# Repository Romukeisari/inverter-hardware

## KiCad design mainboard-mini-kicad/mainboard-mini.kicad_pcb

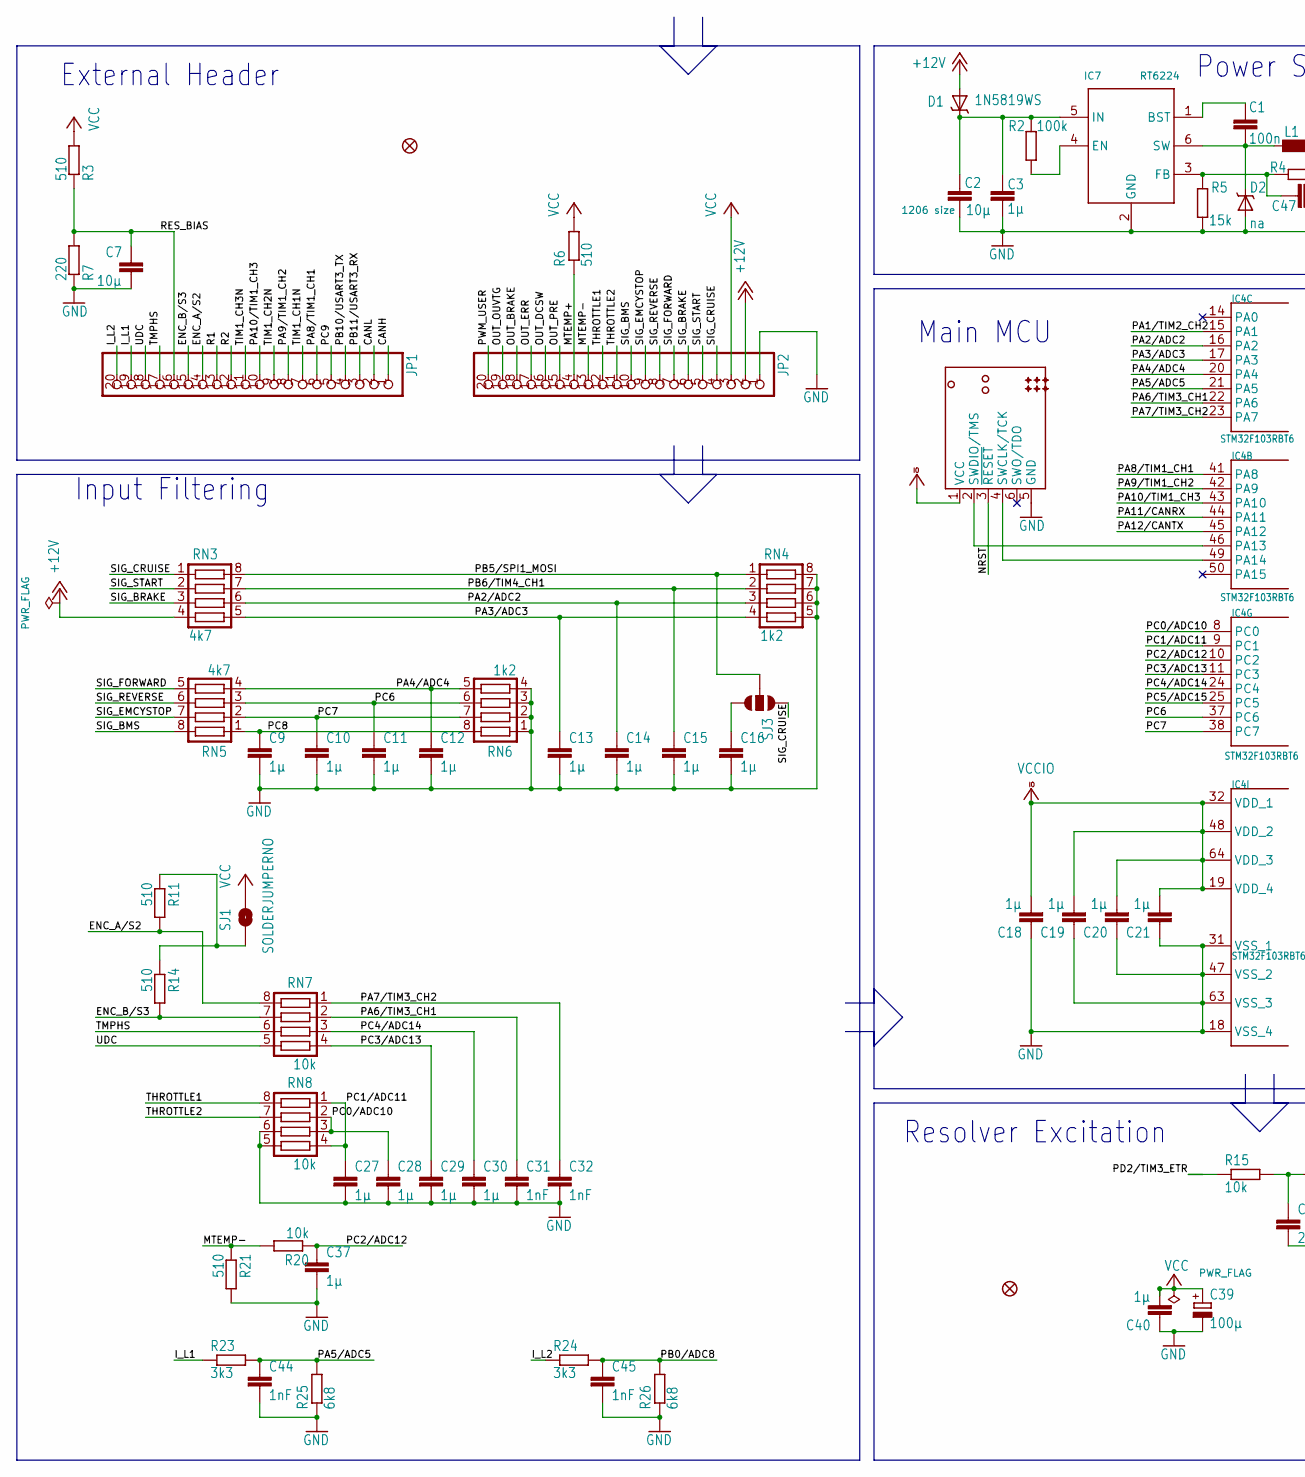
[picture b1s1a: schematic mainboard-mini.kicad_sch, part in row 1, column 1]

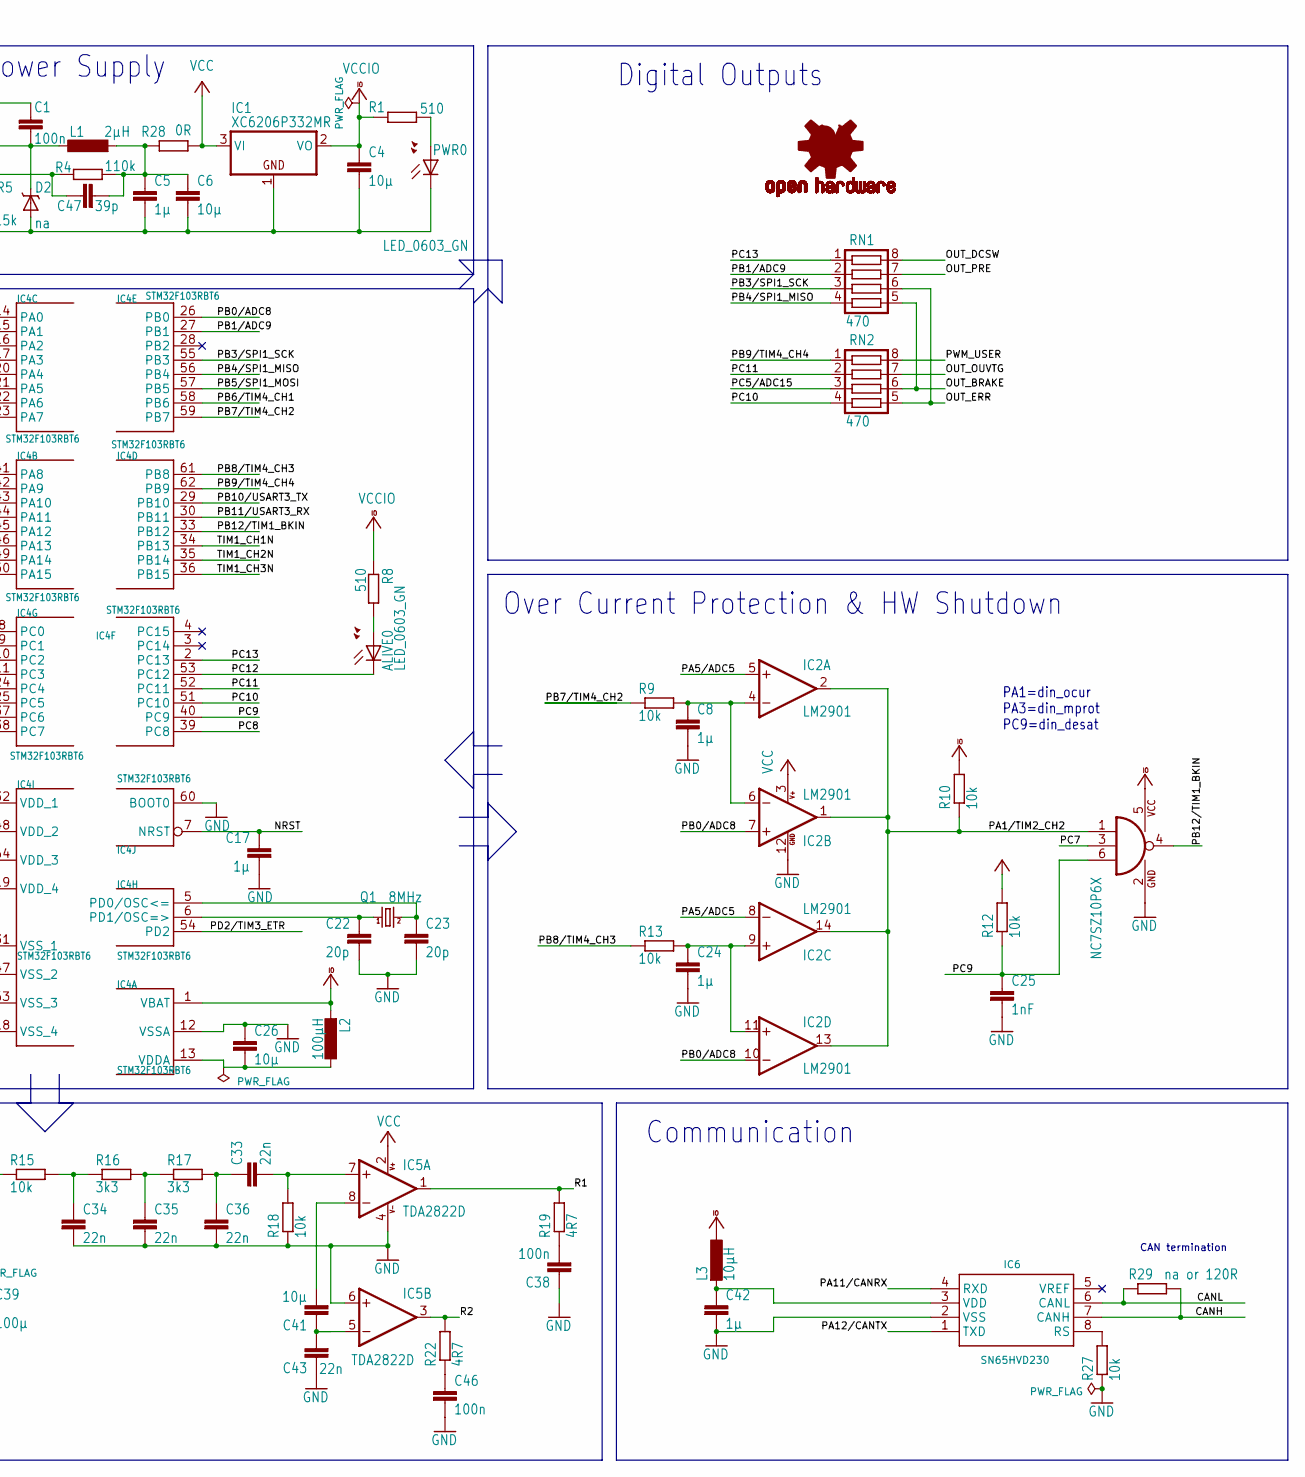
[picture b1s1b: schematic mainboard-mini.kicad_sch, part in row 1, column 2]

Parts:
ALIVE0: LED_0603_GN; SML0805
C1, C38, C46: 100n; C0603
C2: 10µ; C_1206_3216Metric
C3, C5, C8, C9, C10, C11, C12, C13, C14, C15, C16, C17, C18, C19, C20, C21, C24, C27, C28, C29, C30, C37, C40, C42: 1µ; C0603
C4, C6, C7, C26, C41: 10µ; C0603
C22, C23: 20p; C0603
C25, C31, C32, C44, C45: 1nF; C0603
C33, C34, C35, C36, C43: 22n; C0603
C39: 100µ; B_3528-21R
C47: 39p; C_0603_1608Metric
D1: 1N5819WS; SOD-323
D2: na; SOD-323
FID1, FID2: FIDUCIAL1X2.5; FIDUCIAL-1X2.5
IC1: XC6206P332MR; SOT23
IC2: LM2901; SO14
IC3: NC7SZ10P6X; SC70-6
IC4: STM32F103RBT6; TQFP64
IC5: TDA2822D; SO08
IC6: SN65HVD230; SO08
IC7: RT6224; SOT23-6
J1: TC2030_SWD-MCP; TC2030-MCP
JP1, JP2: PINHD-1X20; 1X20
L1: 2µH; L2825P
L2: 100µH; L2012C
L3: 10µH; L2012C
LOGO1: OSHW-LOGOM; OSHW-LOGO-M
PWR0: LED_0603_GN; SML0805
Q1: 8MHz; CRYSTAL-TXC-7A
R1, R3, R6, R8, R11, R14, R21: 510; R0603
R2: 100k; R0603
R4: 110k; R0603
R5: 15k; R0603
R7: 220; R0603
R9, R10, R12, R13, R15, R18, R20, R27: 10k; R0603
R16, R17, R23, R24: 3k3; R0603
R19, R22: 4R7; R0603
R25, R26: 6k8; R0603
R28: 0R; R_0805_2012Metric
R29: na or 120R; R_0603_1608Metric
RN1, RN2: 470; CTS742C083
RN3, RN5: 4k7; CTS742C083
RN4, RN6: 1k2; CTS742C083
RN7, RN8: 10k; CTS742C083
SJ1: SOLDERJUMPERNO; SJ_2S-NO
SJ3: SOLDERJUMPER_2WAYPASTE2&3; SJ_3_PASTE2&3

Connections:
+12V: D1.2 (A), JP2.2, RN3.4
/CANH: IC6.7 (CANH), JP1.1, R29.2
/CANL: IC6.6 (CANL), JP1.2, R29.1
/ENC_A/S2: JP1.14, R11.2, RN7.8
/ENC_B/S3: JP1.15, R14.2, RN7.7
/I_L1: JP1.19, R23.1
/I_L2: JP1.20, R24.1
/MTEMP+: JP2.14, R6.1
/MTEMP-: JP2.13, R20.2, R21.1
/NRST: C17.1, IC4.7 (NRST), J1.3 (~RESET)
/OUT_BRAKE: JP2.18, RN1.5, RN2.6
/OUT_DCSW: JP2.16, RN1.8
/OUT_ERR: JP2.17, RN1.6, RN2.5
/OUT_OUVTG: JP2.19, RN2.7
/OUT_PRE: JP2.15, RN1.7
/PA1/TIM2_CH2: IC2.1 (OUT), IC2.2 (OUT), IC2.13 (OUT), IC2.14 (OUT), IC3.1 (I0), IC4.15 (PA1), R10.1
/PA2/ADC2: C14.1, IC4.16 (PA2), RN3.6, RN4.3
/PA3/ADC3: C13.1, IC4.17 (PA3), RN3.5, RN4.4
/PA4/ADC4: C12.1, IC4.20 (PA4), RN5.4, RN6.5
/PA5/ADC5: C44.1, IC2.5 (+IN), IC2.8 (-IN), IC4.21 (PA5), R23.2, R25.2
/PA6/TIM3_CH1: C31.1, IC4.22 (PA6), RN7.2
/PA7/TIM3_CH2: C32.1, IC4.23 (PA7), RN7.1
/PA8/TIM1_CH1: IC4.41 (PA8), JP1.6
/PA9/TIM1_CH2: IC4.42 (PA9), JP1.8
/PA10/TIM1_CH3: IC4.43 (PA10), JP1.10
/PA11/CANRX: IC4.44 (PA11), IC6.4 (RXD)
/PA12/CANTX: IC4.45 (PA12), IC6.1 (TXD)
/PB0/ADC8: C45.1, IC2.7 (+IN), IC2.10 (-IN), IC4.26 (PB0), R24.2, R26.2
/PB1/ADC9: IC4.27 (PB1), RN1.2
/PB3/SPI1_SCK: IC4.55 (PB3), RN1.3
/PB4/SPI1_MISO: IC4.56 (PB4), RN1.4
/PB5/SPI1_MOSI: IC4.57 (PB5), RN3.8, RN4.1, SJ3.2
/PB6/TIM4_CH1: C15.1, IC4.58 (PB6), RN3.7, RN4.2
/PB7/TIM4_CH2: IC4.59 (PB7), R9.1
/PB8/TIM4_CH3: IC4.61 (PB8), R13.1
/PB9/TIM4_CH4: IC4.62 (PB9), RN2.1
/PB10/USART3_TX: IC4.29 (PB10), JP1.4
/PB11/USART3_RX: IC4.30 (PB11), JP1.3
/PB12/TIM1_BKIN: IC3.4 (O), IC4.33 (PB12)
/PC0/ADC10: C28.1, IC4.8 (PC0), RN8.2, RN8.3
/PC1/ADC11: C27.1, IC4.9 (PC1), RN8.1, RN8.4
/PC2/ADC12: C37.1, IC4.10 (PC2), R20.1
/PC3/ADC13: C29.1, IC4.11 (PC3), RN7.4
/PC4/ADC14: C30.1, IC4.24 (PC4), RN7.3
/PC5/ADC15: IC4.25 (PC5), RN2.3
/PC6: C11.1, IC4.37 (PC6), RN5.3, RN6.6
/PC7: C10.1, IC3.3 (I1), IC4.38 (PC7), RN5.2, RN6.7
/PC8: C9.1, IC4.39 (PC8), RN5.1, RN6.8
/PC9: C25.1, IC3.6 (I2), IC4.40 (PC9), JP1.5, R12.1
/PC10: IC4.51 (PC10), RN2.4
/PC11: IC4.52 (PC11), RN2.2
/PC12: ALIVE0.C, IC4.53 (PC12)
/PC13: IC4.2 (PC13), RN1.1
/PD2/TIM3_ETR: IC4.54 (PD2), R15.1
/PWM_USER: JP2.20, RN2.8
/R1: IC5.1 (OUT), JP1.13, R19.2
/R2: IC5.3 (OUT), JP1.12, R22.2
/RES_BIAS: C7.1, JP1.16, R3.1, R7.2
/SIG_BMS: JP2.10, RN5.8
/SIG_BRAKE: JP2.6, RN3.3
/SIG_CRUISE: JP2.4, RN3.1, SJ3.1
/SIG_EMCYSTOP: JP2.9, RN5.7
/SIG_FORWARD: JP2.7, RN5.5
/SIG_REVERSE: JP2.8, RN5.6
/SIG_START: JP2.5, RN3.2
/THROTTLE1: JP2.12, RN8.8
/THROTTLE2: JP2.11, RN8.7
/TIM1_CH1N: IC4.34 (PB13), JP1.7
/TIM1_CH2N: IC4.35 (PB14), JP1.9
/TIM1_CH3N: IC4.36 (PB15), JP1.11
/TMPHS: JP1.17, RN7.6
/UDC: JP1.18, RN7.5
GND: C2.2, C3.2, C4.2, C5.2, C6.2, C7.2, C8.2, C9.2, C10.2, C11.2, C12.2, C13.2, C14.2, C15.2, C16.2, C17.2, C18.1, C19.1, C20.1, C21.1, C22.2, C23.2, C24.2, C25.2, C26.1, C27.2, C28.2, C29.2, C30.2, C31.2, C32.2, C34.2, C35.2, C36.2, C37.2, C38.1, C39.-, C40.1, C42.2, C43.1, C44.2, C45.2, C46.2, D2.2 (A), IC1.1 (GND), IC2.12 (GND), IC3.2 (GND), IC4.12 (VSSA), IC4.18 (VSS_4), IC4.31 (VSS_1), IC4.47 (VSS_2), IC4.60 (BOOT0), IC4.63 (VSS_3), IC5.4 (V-), IC5.6 (+IN), IC6.2 (VSS), IC7.2 (GND), J1.5 (GND), JP2.1, PWR0.C, R5.1, R7.1, R18.1, R21.2, R25.1, R26.1, R27.1, RN4.5, RN4.6, RN4.7, RN4.8, RN6.1, RN6.2, RN6.3, RN6.4, RN8.5, RN8.6
unnamed: ALIVE0.A, R8.2
unnamed: C16.1, SJ3.3
unnamed: C33.1, C36.1, R17.2
unnamed: C34.1, R15.2, R16.1
unnamed: C35.1, R16.2, R17.1
unnamed: C38.2, R19.1
unnamed: C46.1, R22.1
unnamed: C5.1, C6.1, C47.2, L1.2, R4.1, R28.2
unnamed: C2.1, C3.1, D1.1 (C), IC7.5 (IN), R2.2
unnamed: C1.2, D2.1 (C), IC7.6 (SW), L1.1
unnamed: C8.1, IC2.4 (-IN), IC2.6 (-IN), R9.2
unnamed: C24.1, IC2.9 (+IN), IC2.11 (+IN), R13.2
unnamed: C26.2, IC4.13 (VDDA), L2.1
unnamed: IC4.46 (PA13), J1.2 (SWDIO/TMS)
unnamed: IC4.49 (PA14), J1.4 (SWCLK/TCK)
unnamed: C23.1, IC4.5 (PD0/OSC<=), Q1.P$2 (2)
unnamed: C22.1, IC4.6 (PD1/OSC=>), Q1.P$1 (1)
unnamed: C33.2, IC5.7 (+IN), R18.2
unnamed: C41.2, IC5.8 (-IN)
unnamed: C41.1, C43.2, IC5.5 (-IN)
unnamed: IC6.8 (RS), R27.2
unnamed: C42.1, IC6.3 (VDD), L3.2
unnamed: C1.1, IC7.1 (BST)
unnamed: IC7.4 (EN), R2.1
unnamed: C47.1, IC7.3 (FB), R4.2, R5.2
unnamed: PWR0.A, R1.2
unnamed: R11.1, R14.1, SJ1.1
VCC: C39.+, C40.2, IC1.3 (VI), IC2.3 (V+), IC5.2 (V+), JP2.3, R3.2, R6.2, R12.2, R28.1, SJ1.2
VCCIO: C4.1, C18.2, C19.2, C20.2, C21.2, IC1.2 (VO), IC3.5 (VCC), IC4.1 (VBAT), IC4.19 (VDD_4), IC4.32 (VDD_1), IC4.48 (VDD_2), IC4.64 (VDD_3), J1.1 (VCC), L2.2, L3.1, R1.1, R8.1, R10.2

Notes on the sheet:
Power Supply
CAN termination
Digital Outputs
PA1=din_ocur PA3=din_mprot PC9=din_desat
Main MCU
External Header
Over Current Protection & HW Shutdown
Communication
Input Filtering
Resolver Excitation

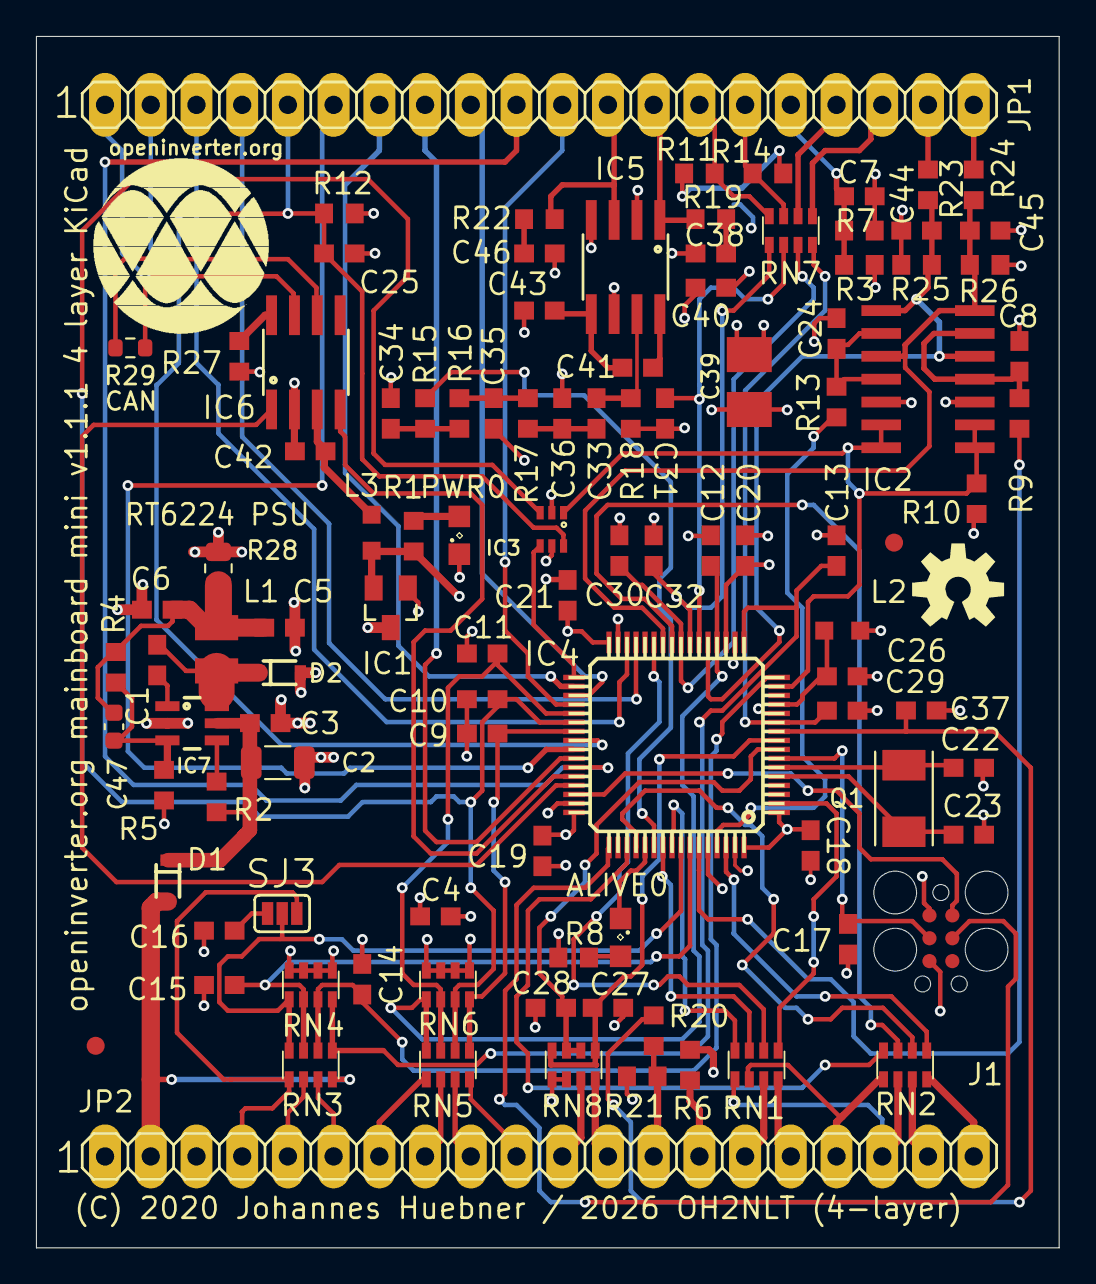
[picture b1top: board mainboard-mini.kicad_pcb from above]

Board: 4 copper layers, 56.8 x 67.3 mm, 108 parts (1 on the bottom side), 102 nets.

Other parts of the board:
U$2: OI_LOGO

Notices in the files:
mainboard-mini-kicad/mainboard-mini.kicad_pcb:
(C) 2020 Johannes Huebner / 2026 OH2NLT (4-layer)
parts and their libraries:
PADDescription 1MCLR/Vpp 2Vdd 3GND 4PGD (ISPDAT) 5PGC (ISPCLK) 6nc (used for LVP) ©2009 ROFA.cz - modified and updated by Robert Darlington ‹rdarlington@gmail.com›
